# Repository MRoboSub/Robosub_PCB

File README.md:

# Robosub_PCB
Where all the electrical PCBs can be found!

## Adding Files
- Right now, KiCad is the standard for PCB design for ease of use.
- Each folder should contain the necessary components and proper versioning. 
- Please add a README file which contains the essential information and any useful tips for future users.
- Contact information is optional but can be extremely useful!!!

## Current Goals
- Simple hall effect + led board
- Smart power rail/ regulators?

## Completed
- Battery indicator

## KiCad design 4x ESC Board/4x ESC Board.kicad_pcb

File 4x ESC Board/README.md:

# 4x ESC Board

This is designed to hold 4 of the BlueRobotics Basic ESC which have their PWM signals routes via an RJ45 port. There are two positions to attach the RJ45 port, and they are wired identically.

An indicator LED shows that the controller board is active. Each ESC has a fuse and traces sufficient for any current needed.

When assembling each board, the exposed copper traces need to be covered with a thick layer of solder tin. This acts as a super cheap way to handle high currents.

## Components
### Terminals:
- 8x TB009-508-03BE
- 4x TB009-508-02BE
- 1x XT60PW-M
### Fuse Holders:
- 4x PTF-76-10
### RJ45 Ports:
- 1x 855055113 (2 positions available on board)
### LED Indicator Setups (OPTIONAL, SMD):
- 1x L78L05_SOT89
- 4x (360, 1k, 10k ohm) 805 resistors
- 4x 805 LED (any color)
- 4x MMBT3904T-7-F

## Plans
- Make RJ45 paired correctly (oops)
- Improve compactness
- Make indicator circuit easy to solder by hand
- Include more protection features!

## Contact
For any questions, feel free to message me via my number or send me an email:- (586) 255-5422 kchirco@umich.edu

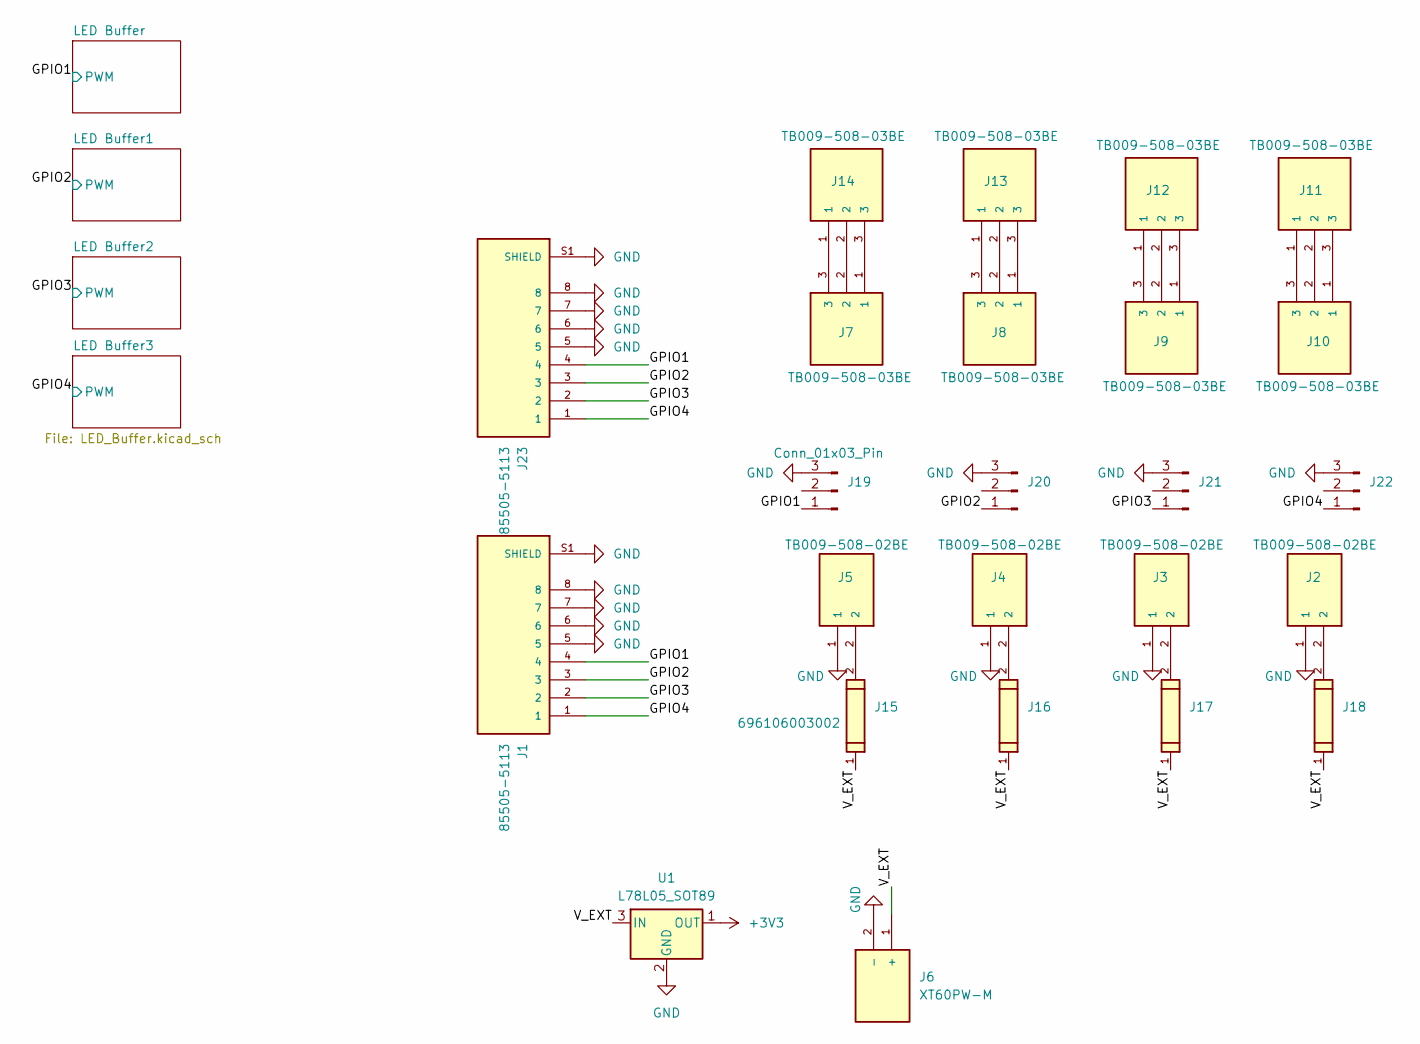
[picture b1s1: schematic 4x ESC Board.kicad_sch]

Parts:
J1, J23: 85505-5113; MOLEX_85505-5113; PARTREV H1
J2, J3, J4, J5: TB009-508-02BE; CUI_TB009-508-02BE
J6: XT60PW-M; AMASS_XT60PW-M; PARTREV V1.2
J7, J8, J9, J10, J11, J12, J13, J14: TB009-508-03BE; CUI_TB009-508-03BE; DigiKey_Part_Number 102-6228-ND
J15, J16, J17, J18: 696106003002; DigiKey_Part_Number 732-11374-ND
J19, J20, J21, J22: Conn_01x03_Pin; PinHeader_1x03_P2.54mm_Vertical
U1: L78L05_SOT89; SOT-89-3

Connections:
+3V3: U1.1 (OUT); also elsewhere on the board
/GPIO1: J1.4, J19.1, J23.4; also elsewhere on the board
/GPIO2: J1.3, J20.1, J23.3; also elsewhere on the board
/GPIO3: J1.2, J21.1, J23.2; also elsewhere on the board
/GPIO4: J1.1, J22.1, J23.1; also elsewhere on the board
/V_EXT: J6.1 (+), J15.1, J16.1, J17.1, J18.1, U1.3 (IN)
GND: J1.5, J1.6, J1.7, J1.8, J1.S1 (SHIELD), J1.S2 (SHIELD), J2.1, J3.1, J4.1, J5.1, J6.2 (-), J19.3, J20.3, J21.3, J22.3, J23.5, J23.6, J23.7, J23.8, J23.S1 (SHIELD), J23.S2 (SHIELD), U1.2 (GND); also elsewhere on the board
unnamed: J10.1, J11.3
unnamed: J10.2, J11.2
unnamed: J10.3, J11.1
unnamed: J9.3, J12.1
unnamed: J9.2, J12.2
unnamed: J9.1, J12.3
unnamed: J8.3, J13.1
unnamed: J8.2, J13.2
unnamed: J8.1, J13.3
unnamed: J7.3, J14.1
unnamed: J7.2, J14.2
unnamed: J7.1, J14.3
unnamed: J5.2, J15.2
unnamed: J4.2, J16.2
unnamed: J3.2, J17.2
unnamed: J2.2, J18.2

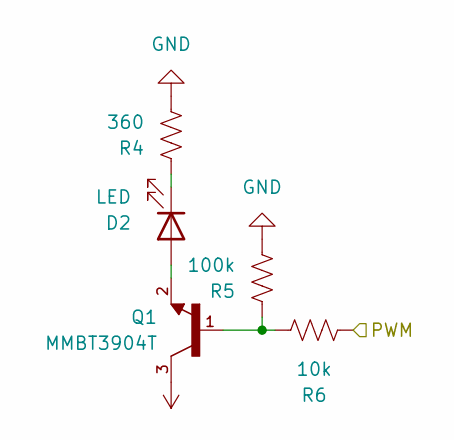
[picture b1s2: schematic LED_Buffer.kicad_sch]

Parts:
D2: LED; LED_0805_2012Metric_Pad1.15x1.40mm_HandSolder
Q1: MMBT3904T; SOT50P160X78-3N; PARTREV 1.0.0
R4: 360; R_0805_2012Metric_Pad1.20x1.40mm_HandSolder
R5: 100k; R_0805_2012Metric_Pad1.20x1.40mm_HandSolder
R6: 10k; R_0805_2012Metric_Pad1.20x1.40mm_HandSolder

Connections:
+3V3: Q1.3; also elsewhere on the board
/GPIO1: R6.2; also elsewhere on the board
GND: R4.2, R5.2; also elsewhere on the board
unnamed: D2.2 (A), Q1.2
unnamed: D2.1 (K), R4.1
unnamed: Q1.1, R5.1, R6.1

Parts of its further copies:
D1, D3, D4: LED; LED_0805_2012Metric_Pad1.15x1.40mm_HandSolder
Q2, Q3, Q4: MMBT3904T; SOT50P160X78-3N; PARTREV 1.0.0
R1, R7, R10: 360; R_0805_2012Metric_Pad1.20x1.40mm_HandSolder
R2, R8, R11: 100k; R_0805_2012Metric_Pad1.20x1.40mm_HandSolder
R3, R9, R12: 10k; R_0805_2012Metric_Pad1.20x1.40mm_HandSolder

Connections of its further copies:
+3V3: Q2.3, Q3.3, Q4.3; also elsewhere on the board
/GPIO2: R3.2; also elsewhere on the board
/GPIO3: R9.2; also elsewhere on the board
/GPIO4: R12.2; also elsewhere on the board
GND: R1.2, R2.2, R7.2, R8.2, R10.2, R11.2; also elsewhere on the board
unnamed: D1.2 (A), Q2.2
unnamed: D1.1 (K), R1.1
unnamed: D3.2 (A), Q3.2
unnamed: D3.1 (K), R7.1
unnamed: D4.2 (A), Q4.2
unnamed: D4.1 (K), R10.1
unnamed: Q2.1, R2.1, R3.1
unnamed: Q3.1, R8.1, R9.1
unnamed: Q4.1, R11.1, R12.1

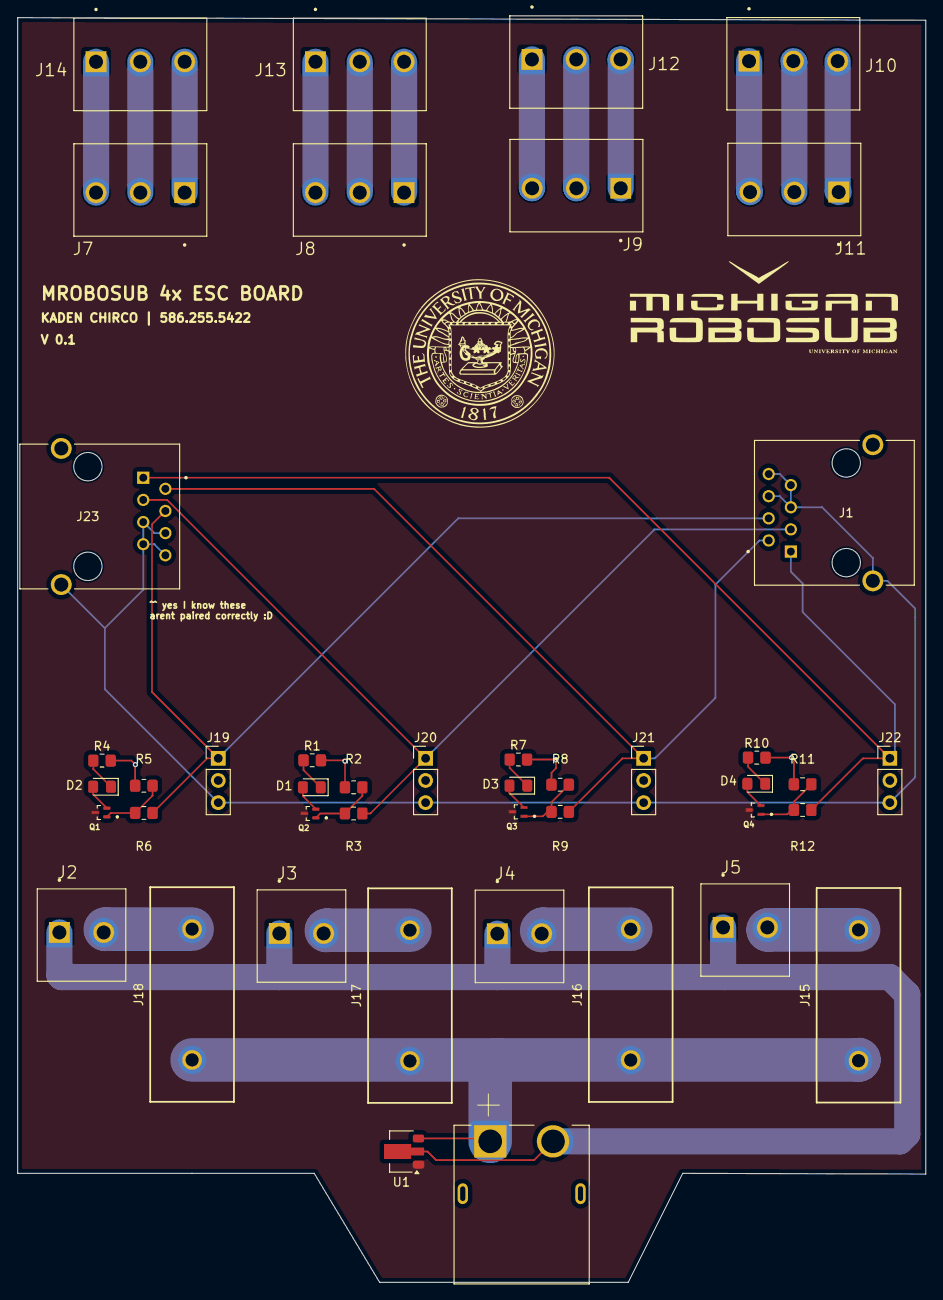
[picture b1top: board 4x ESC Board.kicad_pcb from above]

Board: 2 copper layers, 104.1 x 145.0 mm, 44 parts (0 on the bottom side), 35 nets.

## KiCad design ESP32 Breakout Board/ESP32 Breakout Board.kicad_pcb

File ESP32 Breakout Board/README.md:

# XIAO ESP32 S3 Breakout Board

This board is designed to break out the PWM control wires from the Seeed Studio XIAO ESP32 S3 microcontroller to two RJ45 ports. There is also a place to connect a passive (or active) buzzer for amazing sound effects.

## Components
### Microcontroller:
- 1x Seeed Studio XIAO ESP32 S3
### RJ45 Ports:
- 2x 855055113
### Buzzer (OPTIONAL):
- 1x Passive or Active buzzer 12x9.5RM7.6 (the super common ones you see in Arduino kits)

## Diagram

## Pins and Peripherals
As seen in the diagram above, GPIO 1-8 are used for motor PWM control. GPIO 9 is used for the analog source for the buzzer.

This schematic is designed around the LEDC peripherals and library on the microcontroller. 

DO NOT use the servo libraries, because it often defaults to the motor control peripherals, limiting the output to only a couple of PWM signals rather than 8!

## Plans
- Potentially make this just incorporated onto the ESC board so that we dont have long ethernet cables.

## Contact
For any questions, feel free to message me via my number or send me an email:- (586) 255-5422 kchirco@umich.edu

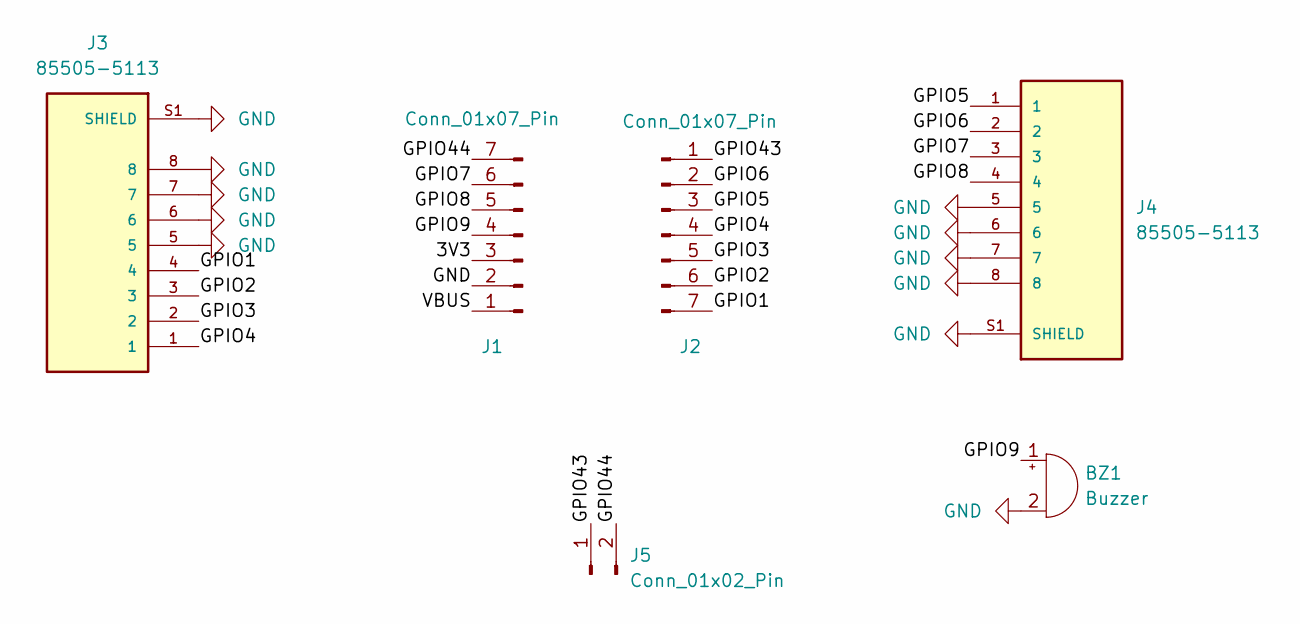
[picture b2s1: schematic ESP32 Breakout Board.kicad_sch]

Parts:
BZ1: Buzzer; Buzzer_12x9.5RM7.6
J1, J2: Conn_01x07_Pin; PinSocket_1x07_P2.54mm_Vertical
J3, J4: 85505-5113; MOLEX_85505-5113; PARTREV H1
J5: Conn_01x02_Pin; PinHeader_1x02_P2.54mm_Vertical

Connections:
/3V3: J1.3
/GPIO1: J2.7, J3.4
/GPIO2: J2.6, J3.3
/GPIO3: J2.5, J3.2
/GPIO4: J2.4, J3.1
/GPIO5: J2.3, J4.1
/GPIO6: J2.2, J4.2
/GPIO7: J1.6, J4.3
/GPIO8: J1.5, J4.4
/GPIO9: BZ1.1 (+), J1.4
/GPIO43: J2.1, J5.1
/GPIO44: J1.7, J5.2
/VBUS: J1.1
GND: BZ1.2 (-), J1.2, J3.5, J3.6, J3.7, J3.8, J3.S1 (SHIELD), J3.S2 (SHIELD), J4.5, J4.6, J4.7, J4.8, J4.S1 (SHIELD), J4.S2 (SHIELD)

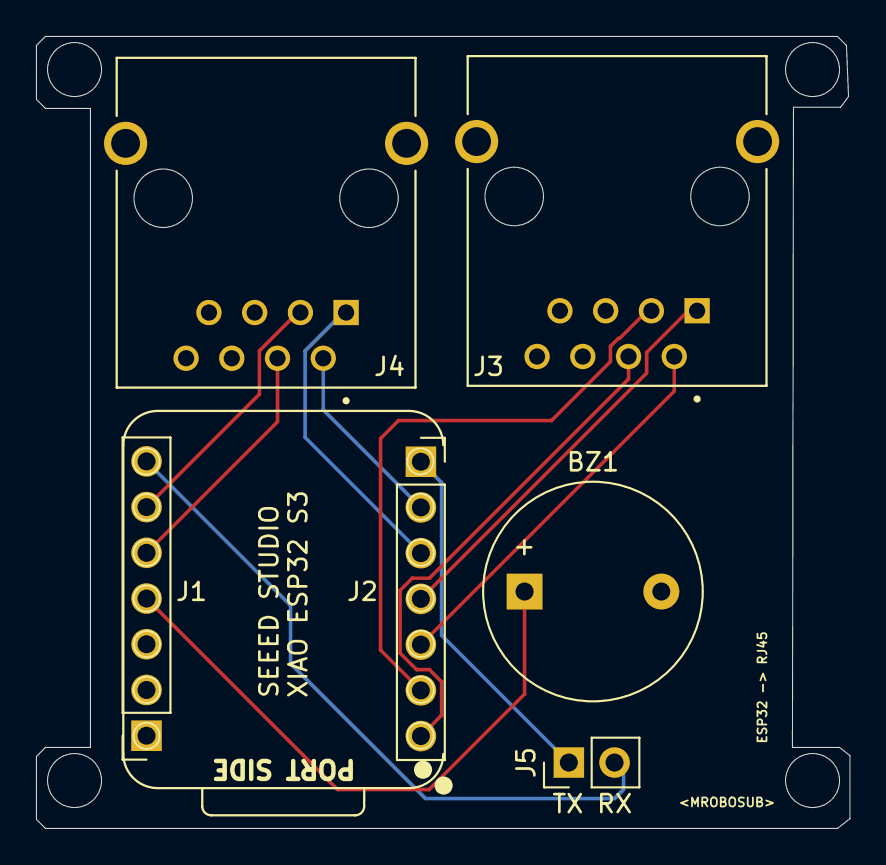
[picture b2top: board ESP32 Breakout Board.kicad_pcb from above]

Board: 2 copper layers, 45.2 x 44.0 mm, 7 parts (0 on the bottom side), 12 nets.

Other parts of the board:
U1: XIAO-ESP32-S3; XIAO-ESP32-S3-DIP

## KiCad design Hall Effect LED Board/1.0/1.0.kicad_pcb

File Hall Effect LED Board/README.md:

# Hall Effect LED Board
This is designed to use a US5881LSE hall effect switch along with a standalone LED.

A 10k pull-up resistor is used on the output to avoid floating, but usually its already done on the microcontroller.

# Plans
- Possibly use 555 timer for flashing LED
- Include a power indicator
  
# Contact
For any questions, feel free to message me via my number or send me an email:-
(586) 255-5422
kchirco@umich.edu

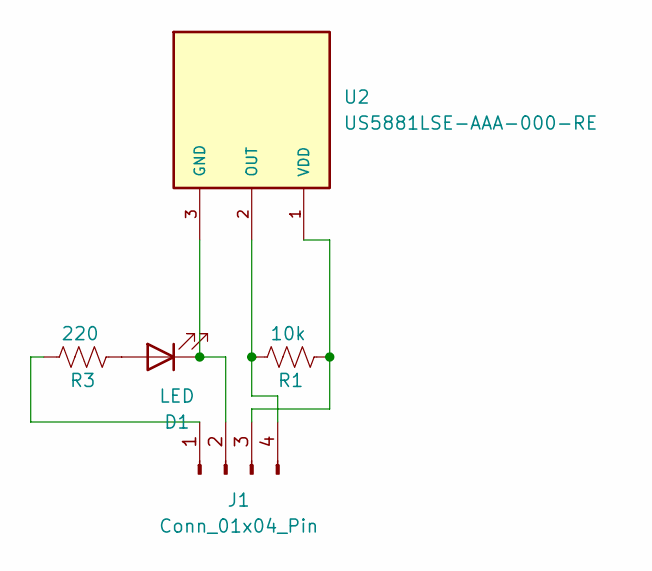
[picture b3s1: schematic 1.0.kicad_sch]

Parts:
D1: LED; LED_0805_2012Metric
J1: Conn_01x04_Pin; PinHeader_1x04_P2.54mm_Vertical
R1: 10k; R_0805_2012Metric_Pad1.20x1.40mm_HandSolder
R3: 220; R_0805_2012Metric_Pad1.20x1.40mm_HandSolder
U2: US5881LSE-AAA-000-RE; SOT95P280X100-3N; PARTREV 005

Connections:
unnamed: D1.2 (A), R3.2
unnamed: D1.1 (K), J1.2, U2.3 (GND)
unnamed: J1.1, R3.1
unnamed: J1.3, R1.2, U2.1 (VDD)
unnamed: J1.4, R1.1, U2.2 (OUT)

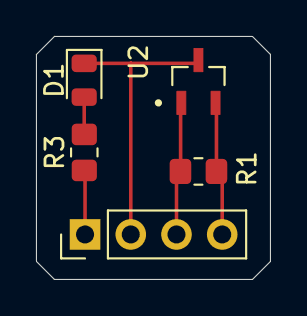
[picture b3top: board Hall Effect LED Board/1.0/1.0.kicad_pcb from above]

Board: 2 copper layers, 13.0 x 13.5 mm, 5 parts (0 on the bottom side), 5 nets.

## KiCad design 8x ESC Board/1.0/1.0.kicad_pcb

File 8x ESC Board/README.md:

# 8x ESC Board
This is designed to hold 8 of the BlueRobotics Basic ESC along with a Polulu Mini Maestro 12-Channel Servo Controller.

An indicator LED shows that the controller board is active. Each ESC has a fuse and traces sufficient for any current needed. 

When assembling each board, the exposed copper traces need to be covered with a thick layer of solder tin. This acts as a fairly cheap way to handle high currents. Previously, 8 oz copper was used for the board which was expensive, so this one uses 2 oz copper.

# Plans
- Improve compactness
- No need to overkill the current rating
- More information displayed such as active ESC indicators
- Include more protection features!
- Get fuse holders that actually handle 30 amps
  
# Contact
For any questions, feel free to message me via my number or send me an email:-
(586) 255-5422
kchirco@umich.edu

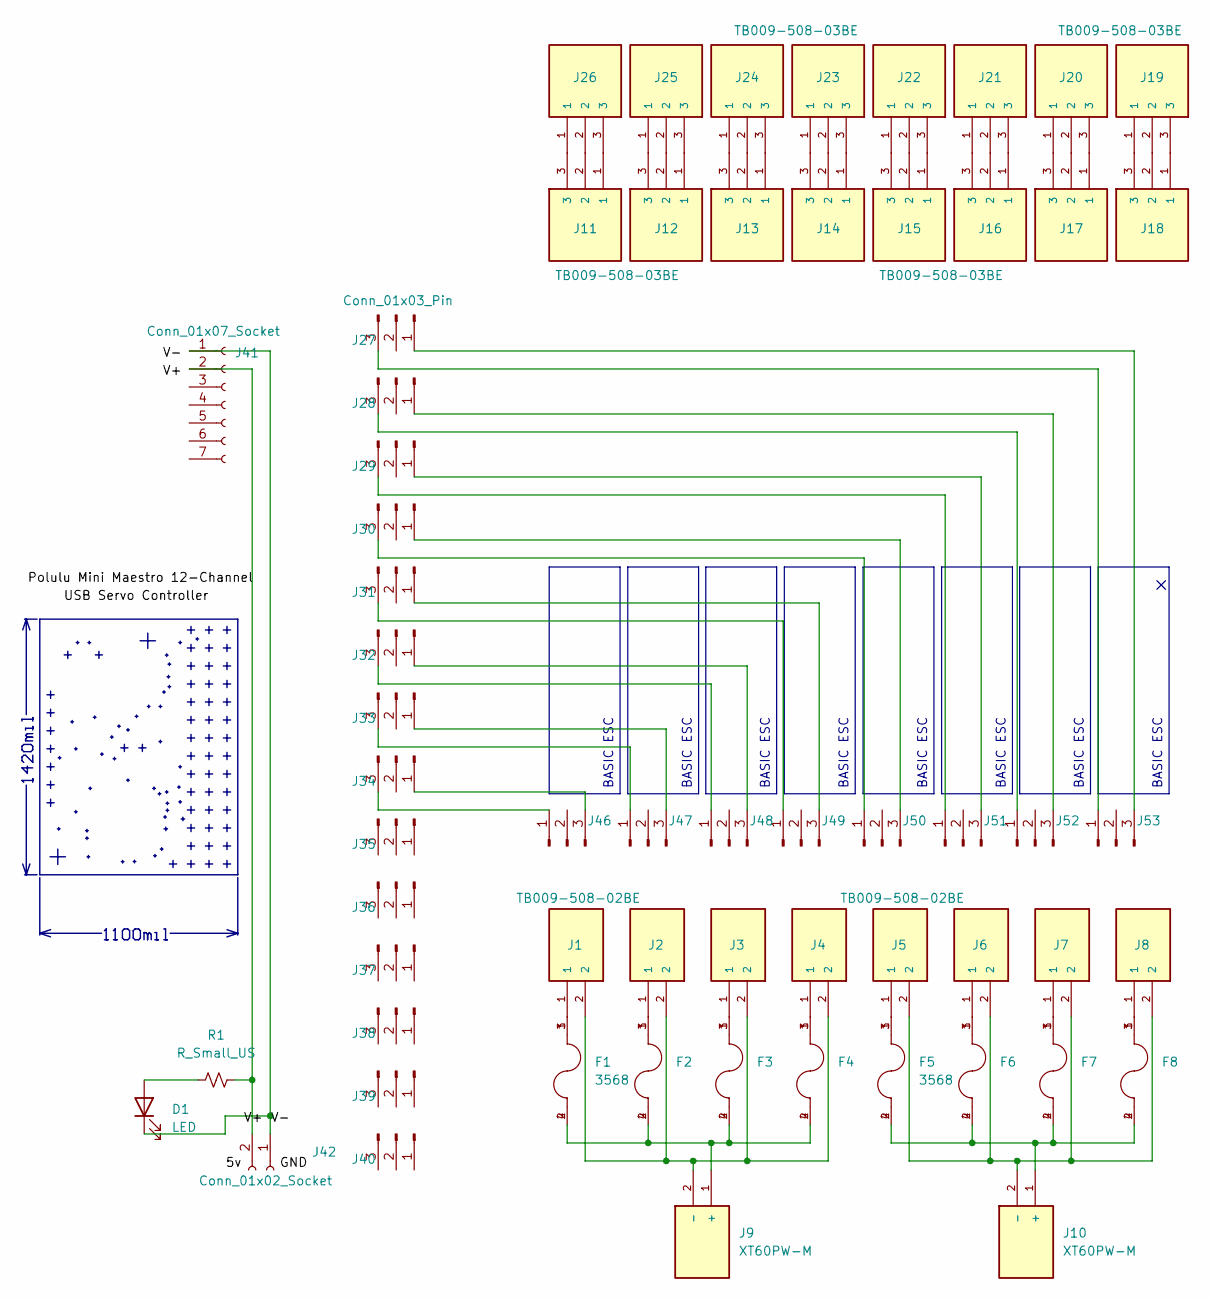
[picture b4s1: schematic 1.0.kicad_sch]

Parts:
D1: LED; LED_D1.8mm_W1.8mm_H2.4mm_Horizontal_O1.27mm_Z4.9mm
F1, F2, F3, F4, F5, F6, F7, F8: 3568; FUSE_3568; PARTREV C
J1, J2, J3, J4, J5, J6, J7, J8: TB009-508-02BE; CUI_TB009-508-02BE
J9, J10: XT60PW-M; AMASS_XT60PW-M; PARTREV V1.2
J11, J12, J13, J14, J15, J16, J17, J18, J19, J20, J21, J22, J23, J24, J25, J26: TB009-508-03BE; CUI_TB009-508-03BE
J27, J28, J29, J30, J31, J32, J33, J34, J35, J36, J37, J38, J39, J40: Conn_01x03_Pin; PinSocket_1x03_P2.54mm_Vertical
J41: Conn_01x07_Socket; PinSocket_1x07_P2.54mm_Vertical
J42: Conn_01x02_Socket; PinSocket_1x02_P2.54mm_Vertical
J46, J47, J48, J49, J50, J51, J52, J53: Conn_01x03_Pin; PinHeader_1x03_P2.54mm_Vertical
R1: R_Small_US; R_Axial_DIN0204_L3.6mm_D1.6mm_P2.54mm_Vertical

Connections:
/V-: D1.1 (K), J41.1, J42.1
unnamed: D1.2 (A), R1.1
unnamed: F1.1, F1.3, J1.1
unnamed: F2.1, F2.3, J2.1
unnamed: F3.1, F3.3, J3.1
unnamed: F4.1, F4.3, J4.1
unnamed: F5.1, F5.3, J5.1
unnamed: F6.1, F6.3, J6.1
unnamed: F7.1, F7.3, J7.1
unnamed: F8.1, F8.3, J8.1
unnamed: F1.2, F1.4, F2.2, F2.4, F3.2, F3.4, F4.2, F4.4, J9.1 (+)
unnamed: J1.2, J2.2, J3.2, J4.2, J9.2 (-)
unnamed: F5.2, F5.4, F6.2, F6.4, F7.2, F7.4, F8.2, F8.4, J10.1 (+)
unnamed: J5.2, J6.2, J7.2, J8.2, J10.2 (-)
unnamed: J11.1, J26.3
unnamed: J11.2, J26.2
unnamed: J11.3, J26.1
unnamed: J12.1, J25.3
unnamed: J12.2, J25.2
unnamed: J12.3, J25.1
unnamed: J13.1, J24.3
unnamed: J13.2, J24.2
unnamed: J13.3, J24.1
unnamed: J14.1, J23.3
unnamed: J14.2, J23.2
unnamed: J14.3, J23.1
unnamed: J15.1, J22.3
unnamed: J15.2, J22.2
unnamed: J15.3, J22.1
unnamed: J16.1, J21.3
unnamed: J16.2, J21.2
unnamed: J16.3, J21.1
unnamed: J17.1, J20.3
unnamed: J17.2, J20.2
unnamed: J17.3, J20.1
unnamed: J18.1, J19.3
unnamed: J18.2, J19.2
unnamed: J18.3, J19.1
unnamed: J27.1, J53.3
unnamed: J27.3, J53.1
unnamed: J28.1, J52.3
unnamed: J28.3, J52.1
unnamed: J29.1, J51.3
unnamed: J29.3, J51.1
unnamed: J30.1, J50.3
unnamed: J30.3, J50.1
unnamed: J31.1, J49.3
unnamed: J31.3, J49.1
unnamed: J32.1, J48.3
unnamed: J32.3, J48.1
unnamed: J33.1, J47.3
unnamed: J33.3, J47.1
unnamed: J34.1, J46.3
unnamed: J34.3, J46.1
unnamed: J41.2, J42.2, R1.2

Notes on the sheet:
BASIC ESC

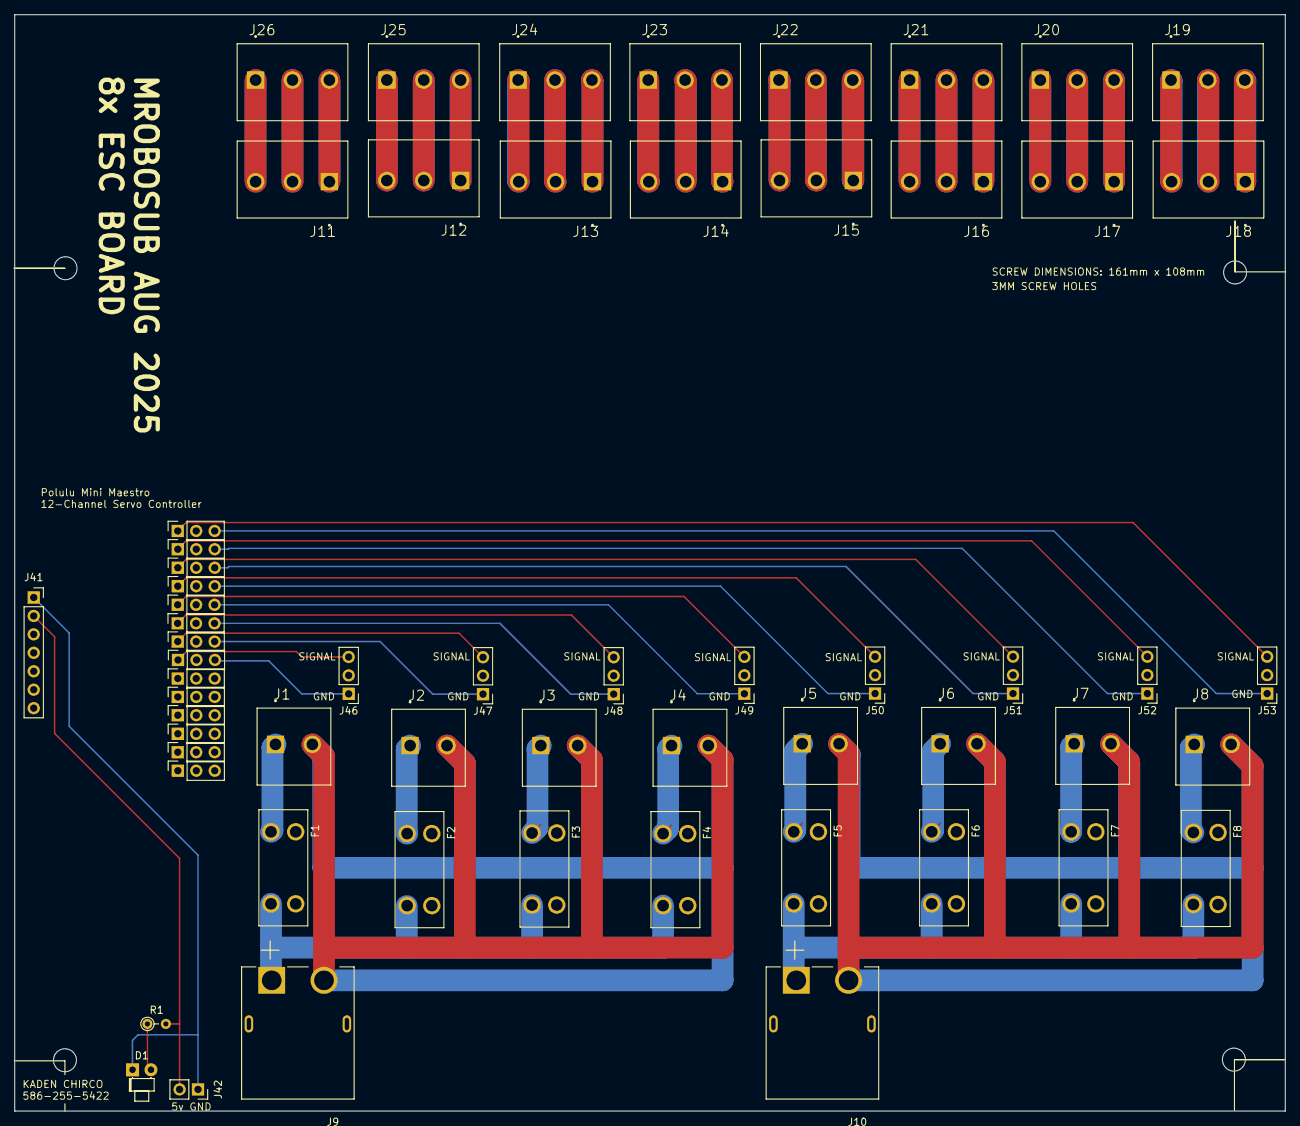
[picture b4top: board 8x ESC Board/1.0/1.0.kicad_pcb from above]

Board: 2 copper layers, 175.0 x 151.0 mm, 60 parts (0 on the bottom side), 55 nets.

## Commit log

2025-08-17 Add 8x ESC Board v1
2025-08-18 Hall Effect LED Board v1
2025-08-18 Set relative project specific components
2025-08-18 Add BVD README
    Battery Voltage Display
2025-09-22 Added 5 volt regulator for others to edit
2025-09-23 Made custom ic symbol and started 3d model
2026-04-27 ESP32 S3 Breakout board and 4x ESC board
2026-04-27 Add initial README with a greeting
2026-04-27 Update README.md with board details and instructions
    Added detailed information about the 4x ESC Board, including components, assembly instructions, and contact information.
2026-04-27 Update README with RJ45 port details
    Clarified RJ45 port attachment details and updated the quantity of RJ45 ports.
2026-04-27 Add README for XIAO ESP32 S3 Breakout Board
    Added detailed information about the XIAO ESP32 S3 Breakout Board, including components, diagram, pin usage, and contact information.
2026-04-27 Fix RJ45 ports description in README.md
2026-04-27 Fix formatting and update battery indicator goal
2026-04-27 Refactor README sections and add completed goals
    Updated README to improve structure and clarity.
